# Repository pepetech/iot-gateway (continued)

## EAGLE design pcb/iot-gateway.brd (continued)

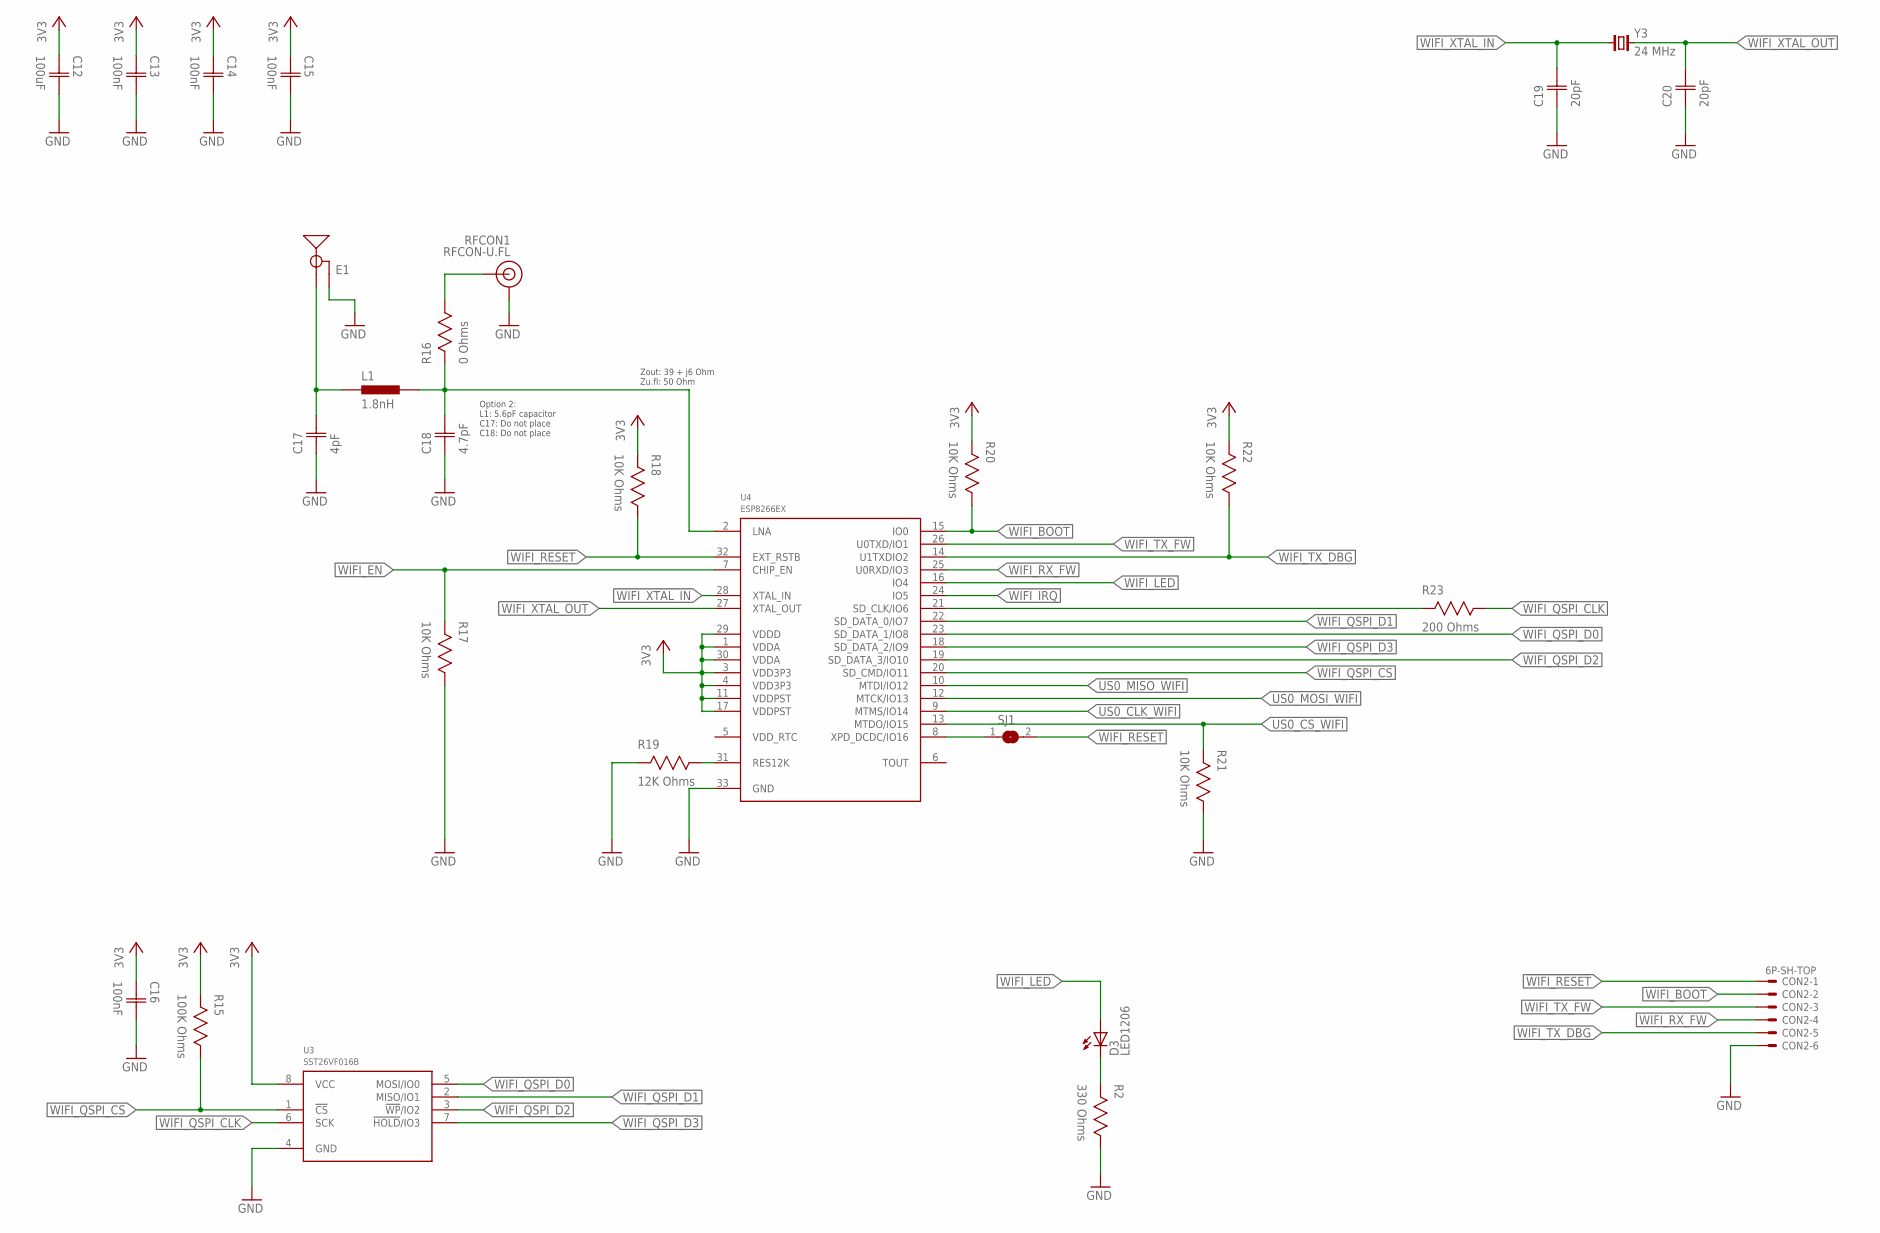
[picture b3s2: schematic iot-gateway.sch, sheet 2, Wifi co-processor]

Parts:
C12: 100uF; CAP1206
C13, C14, C15, C16: 100nF; CAP0603
C17: 4pF; CAP0603
C18: 4.7pF; CAP0603
C19, C20: 20pF; CAP0603
CON2: 6P-SH-TOP; SH-06-TOP
D3: LED1206; 1206
E1: 2.4GHZTRACE-15.2MM; TRACE_ANTENNA_2.4GHZ_15.2MM
L1: 1.8nH; IND0603
R2: 330 Ohms; RES0603
R15: 100K Ohms; RES0603
R16: 0 Ohms; RES0603
R17, R18, R20, R21, R22: 10K Ohms; RES0603
R19: 12K Ohms; RES0603
R23: 200 Ohms; RES0603
RFCON1: RFCON-U.FL; U.FL
SJ1: SJS; SJ_S
U3: SST26VF016B; WSOIC8
U4: ESP8266EX; QFN32
Y3: 24 MHz; 2-SMD-5032

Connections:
3V3: C12.1 (C1), C13.1 (C1), C14.1 (C1), C15.1 (C1), C16.1 (C1), R15.2, R18.2, R20.2, R22.2, U3.8 (VCC), U4.1 (VDDA), U4.3 (VDD3P3), U4.4 (VDD3P3), U4.11 (VDDPST), U4.17 (VDDPST), U4.29 (VDDD), U4.30 (VDDA); also elsewhere on the board
!WIFI_RESET: CON2.1, R18.1, SJ1.2, U4.32 (EXT_RSTB)
GND: C12.2 (C2), C13.2 (C2), C14.2 (C2), C15.2 (C2), C16.2 (C2), C17.1 (C1), C18.1 (C1), C19.1 (C1), C20.1 (C1), CON2.6, E1.GND, R2.1, R17.1, R19.2, R21.1, RFCON1.P$1 (GND), RFCON1.P$2 (GND), U3.4 (GND), U4.33 (GND); also elsewhere on the board
unnamed: R19.1, U4.31 (RES12K)
unnamed: R23.2, U4.21 (SD_CLK/IO6)
unnamed: C18.2 (C2), L1.2, R16.2, U4.2 (LNA)
unnamed: C17.2 (C2), E1.ANT (SIGNAL), L1.1
unnamed: R16.1, RFCON1.P$3 (SIGNAL)
unnamed: SJ1.1, U4.8 (XPD_DCDC/IO16)
unnamed: D3.1 (C), R2.2
US0_CLK_WIFI: U4.9 (MTMS/IO14)
US0_CS_WIFI: R21.2, U4.13 (MTDO/IO15)
US0_MISO_WIFI: U4.10 (MTDI/IO12)
US0_MOSI_WIFI: U4.12 (MTCK/IO13)
WIFI_BOOT: CON2.2, R20.1, U4.15 (IO0)
WIFI_EN: R17.2, U4.7 (CHIP_EN)
WIFI_IRQ: U4.24 (IO5)
WIFI_LED: D3.2 (A), U4.16 (IO4)
WIFI_QSPI_CLK: R23.1, U3.6 (SCK)
WIFI_QSPI_CS: R15.1, U3.1 (!CS!), U4.20 (SD_CMD/IO11)
WIFI_QSPI_D0: U3.5 (MOSI/IO0), U4.23 (SD_DATA_1/IO8)
WIFI_QSPI_D1: U3.2 (MISO/IO1), U4.22 (SD_DATA_0/IO7)
WIFI_QSPI_D2: U3.3 (!WP!/IO2), U4.19 (SD_DATA_3/IO10)
WIFI_QSPI_D3: U3.7 (!HOLD!/IO3), U4.18 (SD_DATA_2/IO9)
WIFI_RX_FW: CON2.4, U4.25 (U0RXD/IO3)
WIFI_TX_DBG: CON2.5, R22.1, U4.14 (U1TXDIO2)
WIFI_TX_FW: CON2.3, U4.26 (U0TXD/IO1)
WIFI_XTAL_IN: C19.2 (C2), U4.28 (XTAL_IN), Y3.1
WIFI_XTAL_OUT: C20.2 (C2), U4.27 (XTAL_OUT), Y3.2

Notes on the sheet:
Option 2: L1: 5.6pF capacitor C17: Do not place C18: Do not place
Zout: 39 + j6 Ohm Zu.fl: 50 Ohm

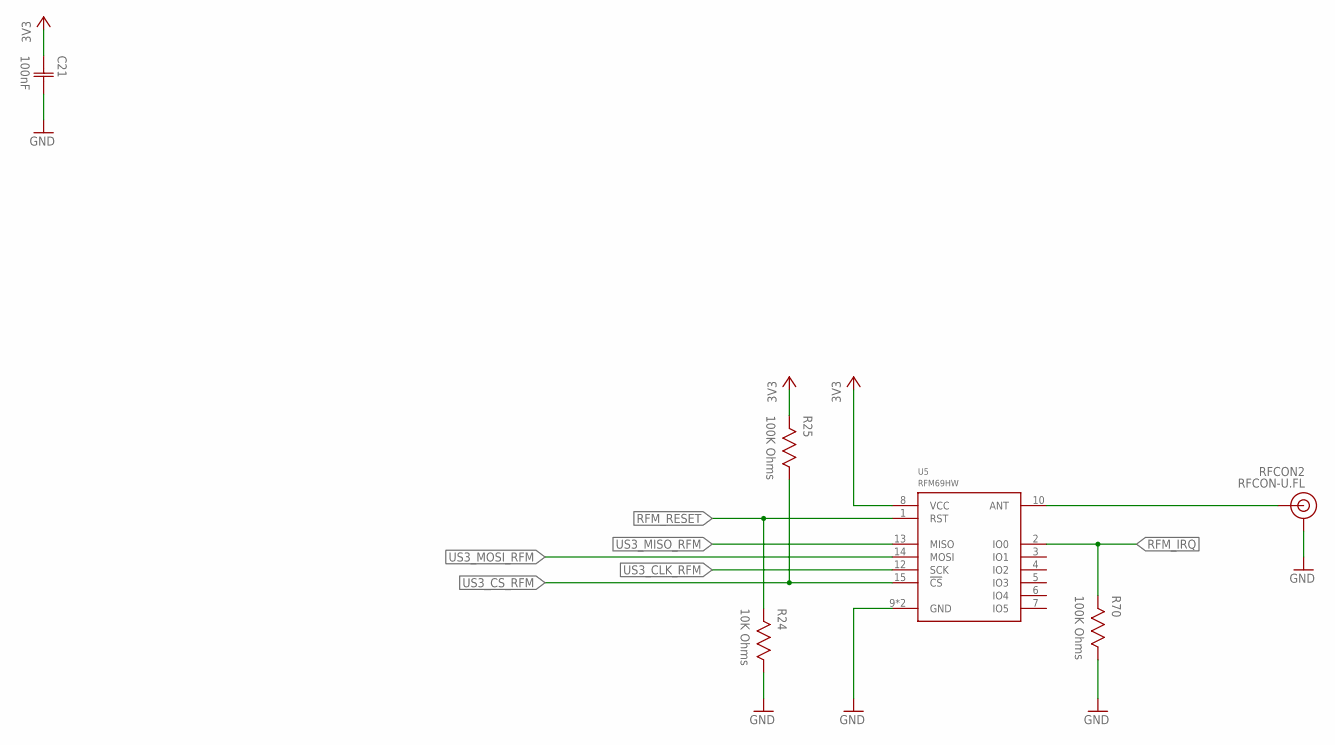
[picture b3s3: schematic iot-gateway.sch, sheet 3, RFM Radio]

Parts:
C21: 100nF; CAP0603
R24: 10K Ohms; RES0603
R25, R70: 100K Ohms; RES0603
RFCON2: RFCON-U.FL; U.FL
U5: RFM69HW; RFM69XW-XXXS2

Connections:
3V3: C21.1 (C1), R25.2, U5.8 (VCC); also elsewhere on the board
GND: C21.2 (C2), R24.1, R70.1, RFCON2.P$1 (GND), RFCON2.P$2 (GND), U5.9 (GND), U5.11 (GND); also elsewhere on the board
unnamed: RFCON2.P$3 (SIGNAL), U5.10 (ANT)
RFM_IRQ: R70.2, U5.2 (IO0)
RFM_RESET: R24.2, U5.1 (RST)
US3_CLK_RFM: U5.12 (SCK)
US3_CS_RFM: R25.1, U5.15 (!CS)
US3_MISO_RFM: U5.13 (MISO)
US3_MOSI_RFM: U5.14 (MOSI)

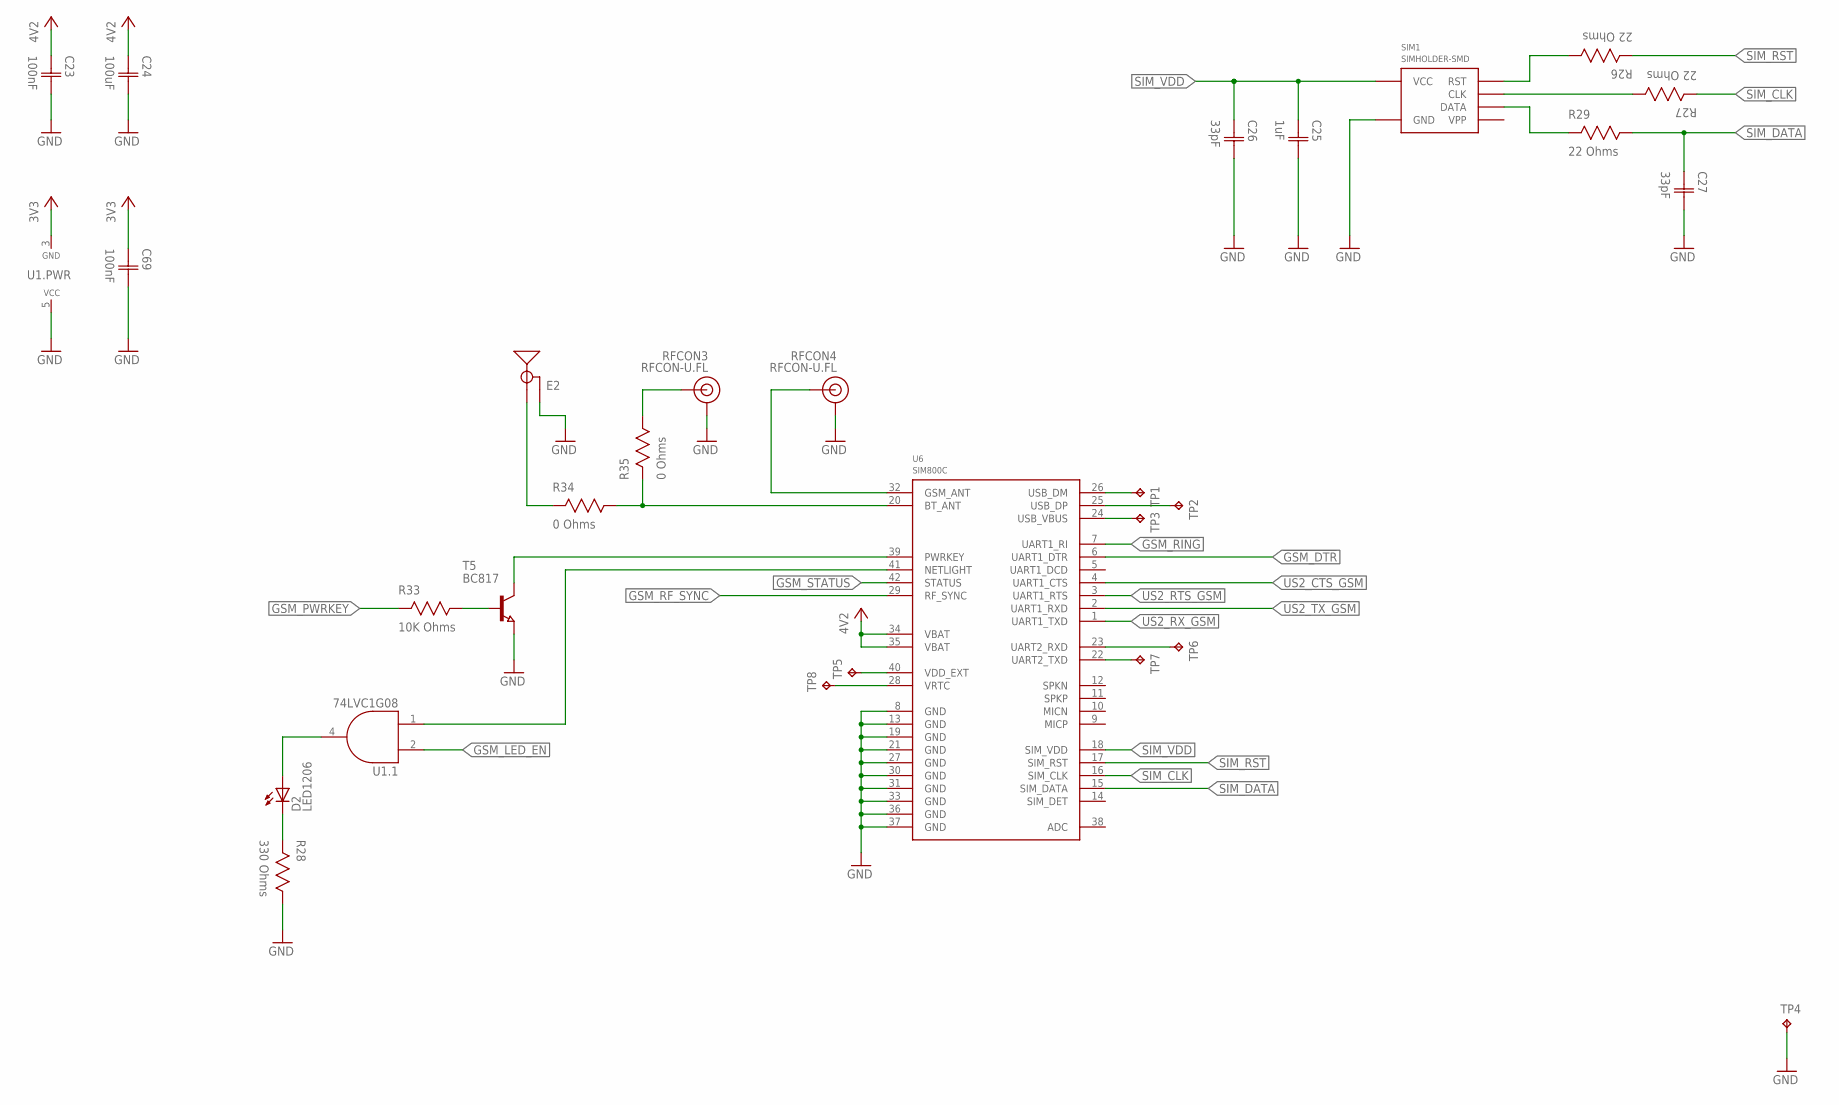
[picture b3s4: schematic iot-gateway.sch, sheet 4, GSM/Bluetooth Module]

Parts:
C23, C69: 100nF; CAP0603
C24: 100uF; CAP1206
C25: 1uF; CAP0603
C26, C27: 33pF; CAP0603
D2: LED1206; 1206
E2: 2.4GHZTRACE-15.2MM; TRACE_ANTENNA_2.4GHZ_15.2MM
R26, R27, R29: 22 Ohms; RES0603
R28: 330 Ohms; RES0603
R33: 10K Ohms; RES0603
R34, R35: 0 Ohms; RES0603
RFCON3, RFCON4: RFCON-U.FL; U.FL
SIM1: SIMHOLDER-SMD
T5: BC817; SOT23
TP1, TP2, TP3, TP4, TP5, TP6, TP7, TP8: TESTPOINT-1.27MM; PAD1.27MM
U1: 74LVC1G08; SC70-5
U6: SIM800C

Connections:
3V3: C69.1 (C1), U1.3 (GND); also elsewhere on the board
4V2: C23.1 (C1), C24.1 (C1), U6.34 (VBAT), U6.35 (VBAT); also elsewhere on the board
!GSM_DTR: U6.6 (UART1_DTR)
!GSM_RING: U6.7 (UART1_RI)
GND: C23.2 (C2), C24.2 (C2), C25.2 (C2), C26.2 (C2), C27.2 (C2), C69.2 (C2), E2.GND, R28.1, RFCON3.P$1 (GND), RFCON3.P$2 (GND), RFCON4.P$1 (GND), RFCON4.P$2 (GND), SIM1.C5 (GND), T5.2 (E), TP4.TP, U1.5 (VCC), U6.8 (GND), U6.13 (GND), U6.19 (GND), U6.21 (GND), U6.27 (GND), U6.30 (GND), U6.31 (GND), U6.33 (GND), U6.36 (GND), U6.37 (GND); also elsewhere on the board
GSM_LED_EN: U1.2 (A)
GSM_PWRKEY: R33.2
GSM_RF_SYNC: U6.29 (RF_SYNC)
GSM_STATUS: U6.42 (STATUS)
unnamed: RFCON4.P$3 (SIGNAL), U6.32 (GSM_ANT)
unnamed: R26.1, SIM1.C2 (RST)
unnamed: U1.1 (B), U6.41 (NETLIGHT)
unnamed: D2.1 (C), R28.2
unnamed: D2.2 (A), U1.4 (Y)
unnamed: R27.1, SIM1.C3 (CLK)
unnamed: R34.1, R35.2, U6.20 (BT_ANT)
unnamed: E2.ANT (SIGNAL), R34.2
unnamed: R35.1, RFCON3.P$3 (SIGNAL)
unnamed: TP8.TP, U6.28 (VRTC)
unnamed: TP1.TP, U6.26 (USB_DM)
unnamed: TP2.TP, U6.25 (USB_DP)
unnamed: T5.3 (C), U6.39 (PWRKEY)
unnamed: R33.1, T5.1 (B)
unnamed: TP3.TP, U6.24 (USB_VBUS)
unnamed: TP5.TP, U6.40 (VDD_EXT)
unnamed: R29.2, SIM1.C7 (DATA)
unnamed: TP6.TP, U6.23 (UART2_RXD)
unnamed: TP7.TP, U6.22 (UART2_TXD)
SIM_CLK: R27.2, U6.16 (SIM_CLK)
SIM_DATA: C27.1 (C1), R29.1, U6.15 (SIM_DATA)
SIM_RST: R26.2, U6.17 (SIM_RST)
SIM_VDD: C25.1 (C1), C26.1 (C1), SIM1.C1 (VCC), U6.18 (SIM_VDD)
US2_CTS_GSM: U6.4 (UART1_CTS)
US2_RTS_GSM: U6.3 (UART1_RTS)
US2_RX_GSM: U6.1 (UART1_TXD)
US2_TX_GSM: U6.2 (UART1_RXD)

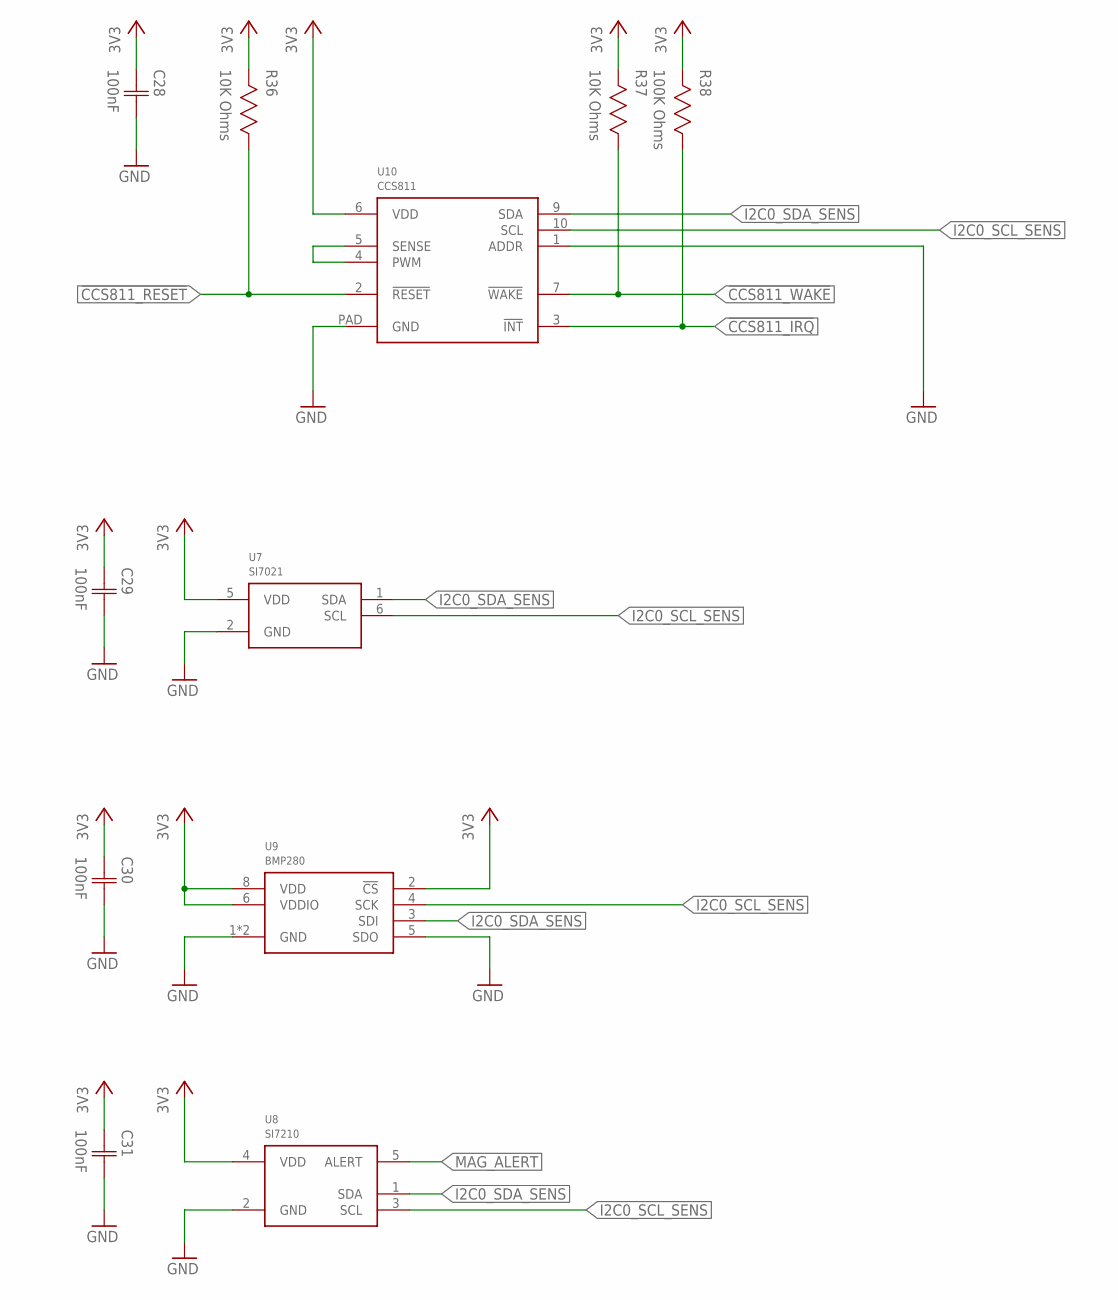
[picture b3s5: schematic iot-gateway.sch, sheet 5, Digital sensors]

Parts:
C28, C29, C30, C31: 100nF; CAP0603
R36, R37: 10K Ohms; RES0603
R38: 100K Ohms; RES0603
U7: SI7021; DFN6
U8: SI7210; SOT23-5
U9: BMP280
U10: CCS811; LGA10

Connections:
3V3: C28.1 (C1), C29.1 (C1), C30.1 (C1), C31.1 (C1), R36.2, R37.2, R38.2, U7.5 (VDD), U8.4 (VDD), U9.2 (!CS), U9.6 (VDDIO), U9.8 (VDD), U10.6 (VDD); also elsewhere on the board
!CCS811_IRQ: R38.1, U10.3 (!INT)
!CCS811_RESET: R36.1, U10.2 (!RESET)
!CCS811_WAKE: R37.1, U10.7 (!WAKE)
GND: C28.2 (C2), C29.2 (C2), C30.2 (C2), C31.2 (C2), U7.2 (GND), U8.2 (GND), U9.1 (GND), U9.5 (SDO), U9.7 (GND), U10.1 (ADDR), U10.PAD (GND); also elsewhere on the board
I2C0_SCL_SENS: U7.6 (SCL), U8.3 (SCL), U9.4 (SCK), U10.10 (SCL); also elsewhere on the board
I2C0_SDA_SENS: U7.1 (SDA), U8.1 (SDA), U9.3 (SDI), U10.9 (SDA); also elsewhere on the board
MAG_ALERT: U8.5 (ALERT)
unnamed: U10.4 (PWM), U10.5 (SENSE)

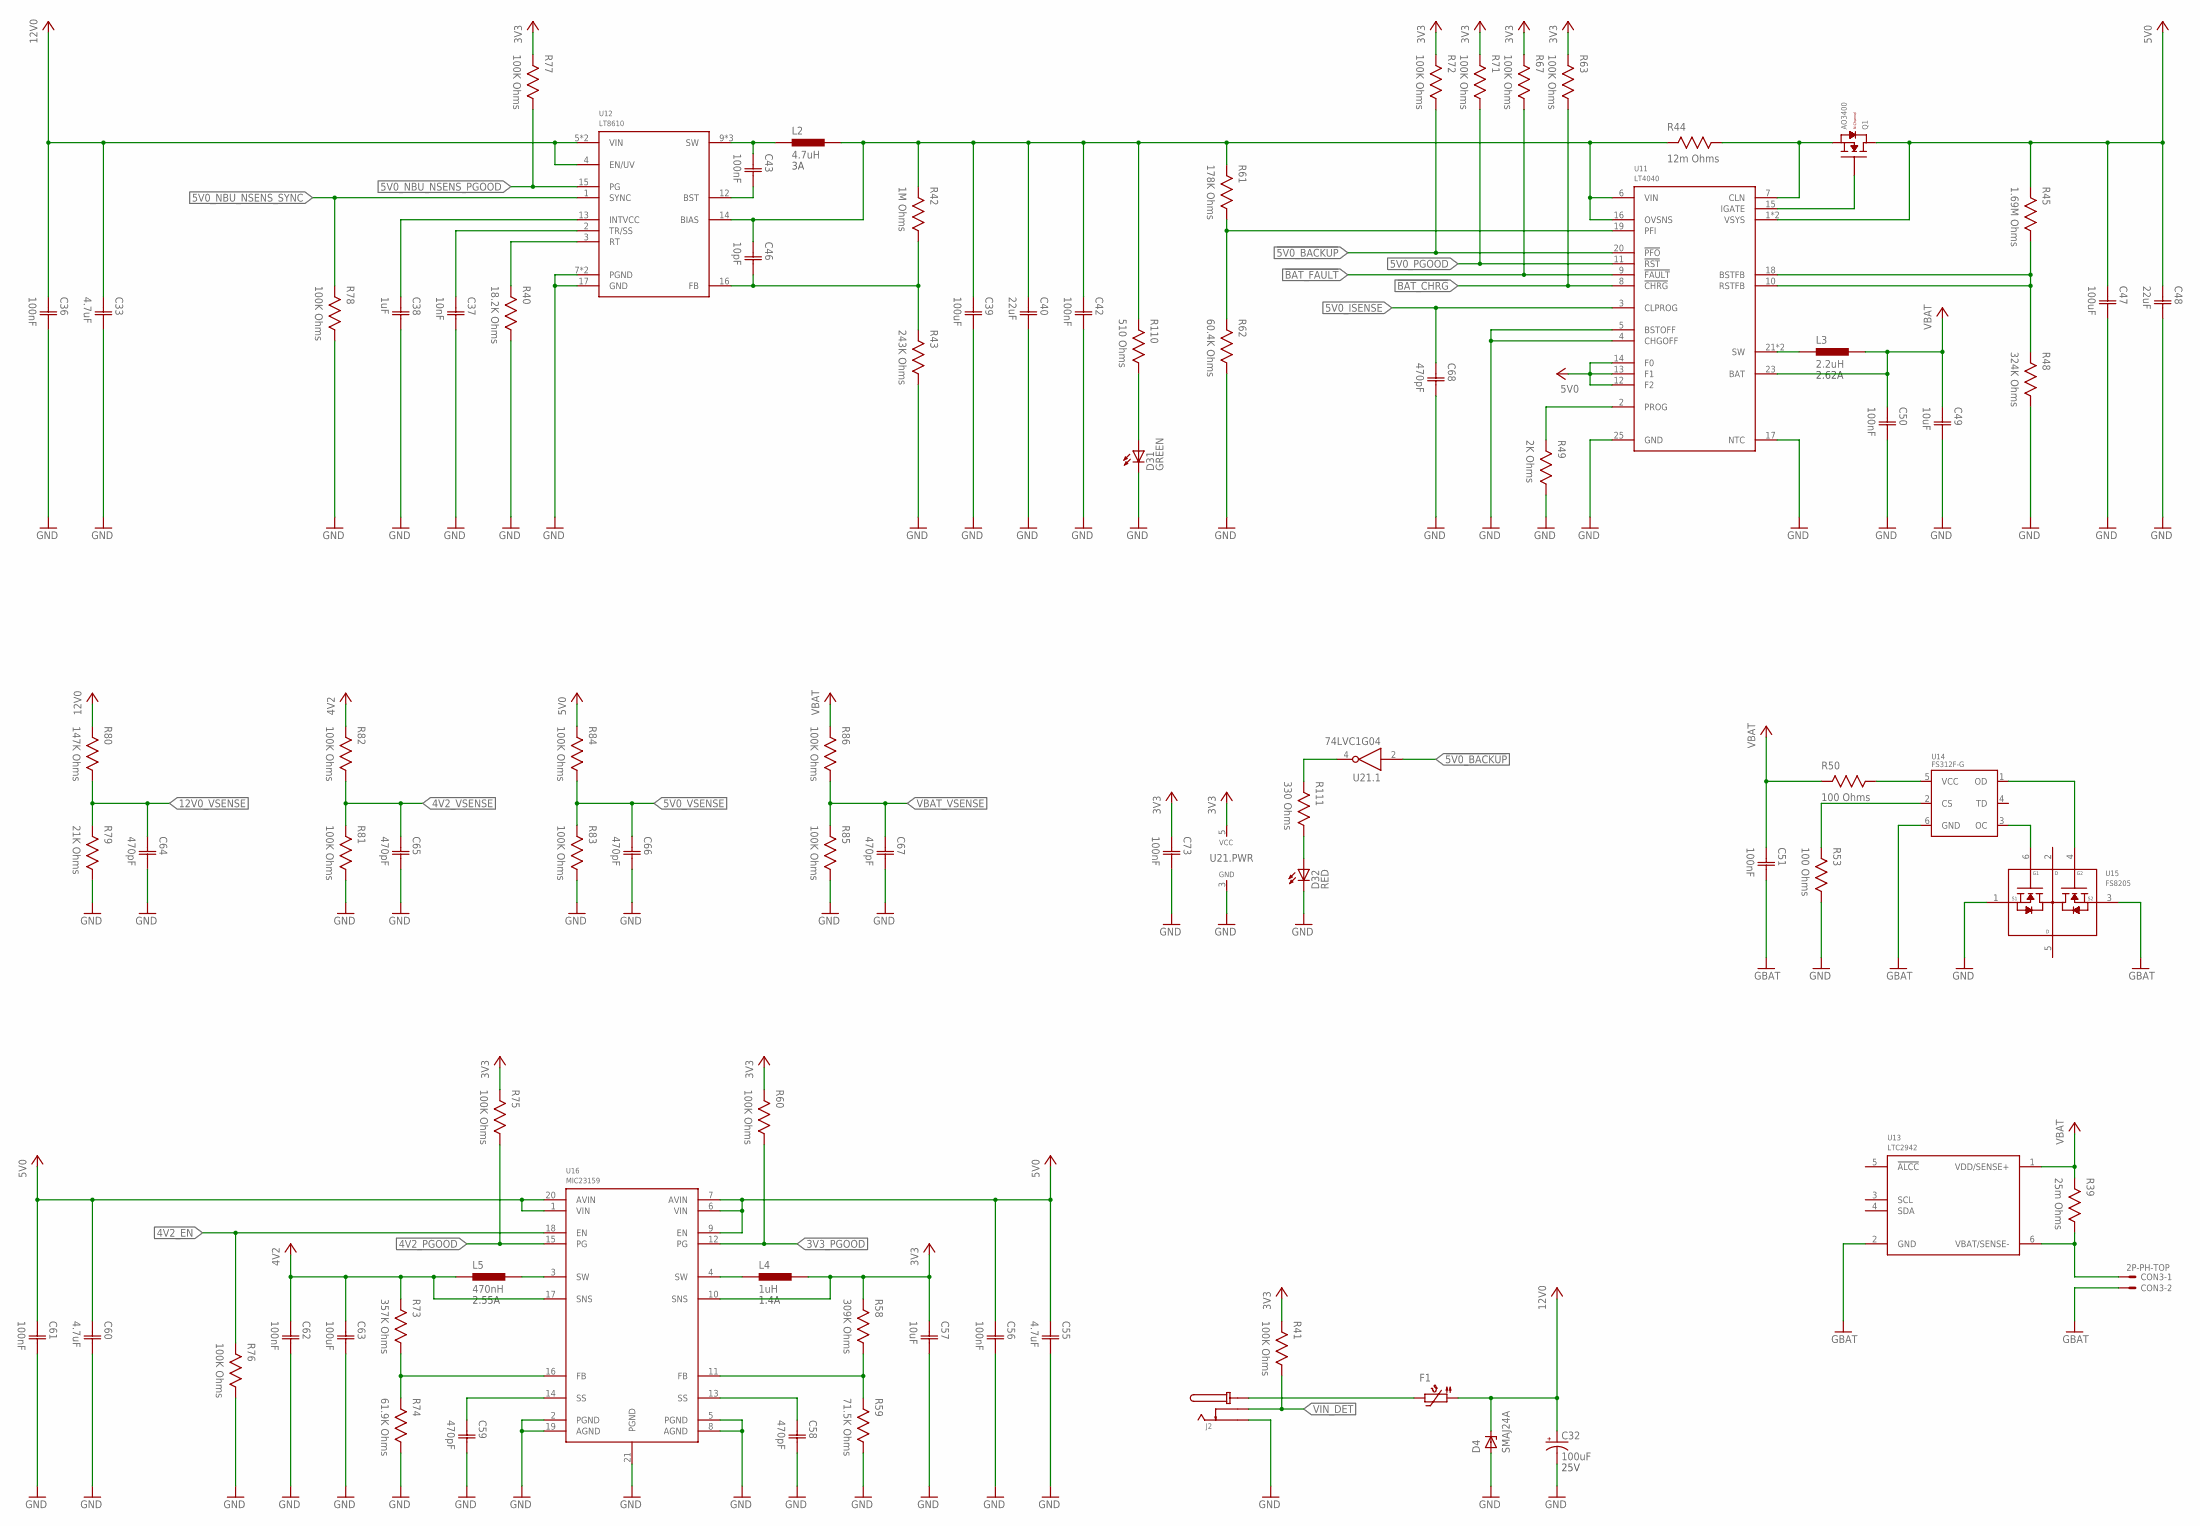
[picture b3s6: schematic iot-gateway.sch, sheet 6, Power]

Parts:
C32: 100uF; AL-CAP-CASE-D; VOLTAGE 25V
C33, C55, C60: 4.7uF; CAP0603
C36, C42, C43, C50, C51, C56, C61, C62, C73: 100nF; CAP0603
C37: 10nF; CAP0603
C38: 1uF; CAP0603
C39, C47, C63: 100uF; CAP1206
C40, C48: 22uF; CAP1206
C46: 10pF; CAP0603
C49, C57: 10uF; CAP0603
C58, C59, C64, C65, C66, C67, C68: 470pF; CAP0603
CON3: 2P-PH-TOP; PH-02-TOP
D4: SMAJ24A; DO214AC
D31: GREEN; 0603
D32: RED; 0603
F1: 2.6A Hold; 1812
J2: DCJACK; DC-050
L2: 4.7uH; IND0606
L3: 2.2uH; IND0505
L4: 1uH; IND0805
L5: 470nH; IND3225
Q1: AO3400; SOT23
R39: 25m Ohms; RES1206
R40: 18.2K Ohms; RES0603
R41, R60, R63, R67, R71, R72, R75, R76, R77, R78, R81, R82, R83, R84, R85, R86: 100K Ohms; RES0603
R42: 1M Ohms; RES0603
R43: 243K Ohms; RES0603
R44: 12m Ohms; RES1206
R45: 1.69M Ohms; RES0603
R48: 324K Ohms; RES0603
R49: 2K Ohms; RES0603
R50, R53: 100 Ohms; RES0603
R58: 309K Ohms; RES0603
R59: 71.5K Ohms; RES0603
R61: 178K Ohms; RES0603
R62: 60.4K Ohms; RES0603
R73: 357K Ohms; RES0603
R74: 61.9K Ohms; RES0603
R79: 21K Ohms; RES0603
R80: 147K Ohms; RES0603
R110: 510 Ohms; RES0603
R111: 330 Ohms; RES0603
U11: LT4040; QFN24_ASYM
U12: LT8610; MSOP16_EP
U13: LTC2942; DFN6
U14: FS312F-G; SOT23-6
U15: FS8205; SOT23-6
U16: MIC23159; VQFN20
U21: 74LVC1G04; SC70-5

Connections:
3V3: C57.1 (C1), C73.1 (C1), L4.2, R41.2, R58.2, R60.2, R63.2, R67.2, R71.2, R72.2, R75.2, R77.2, U16.10 (SNS), U21.5 (VCC); also elsewhere on the board
3V3_FB: R58.1, R59.2, U16.11 (FB)
3V3_PGOOD: R60.1, U16.12 (PG)
4V2: C62.1 (C1), C63.1 (C1), L5.1, R73.2, R82.2, U16.17 (SNS); also elsewhere on the board
4V2_EN: R76.2, U16.18 (EN)
4V2_FB: R73.1, R74.2, U16.16 (FB)
4V2_PGOOD: R75.1, U16.15 (PG)
4V2_VSENSE: C65.1 (C1), R81.2, R82.1
5V0: C47.1 (C1), C48.1 (C1), C55.1 (C1), C56.1 (C1), C60.1 (C1), C61.1 (C1), Q1.3 (D), R45.2, R84.2, U11.1 (VSYS), U11.12 (F2), U11.13 (F1), U11.14 (F0), U11.24 (VSYS), U16.1 (VIN), U16.6 (VIN), U16.7 (AVIN), U16.9 (EN), U16.20 (AVIN); also elsewhere on the board
5V0_FB: R45.1, R48.2, U11.10 (RSTFB), U11.18 (BSTFB)
5V0_ISENSE: C68.1 (C1), U11.3 (CLPROG)
5V0_NBU: Q1.2 (S), R44.1, U11.7 (CLN)
5V0_NBU_NSENS: C39.1 (C1), C40.1 (C1), C42.1 (C1), C46.1 (C1), L2.2, R42.2, R44.2, R61.2, R110.2, U11.6 (VIN), U11.16 (OVSNS), U12.14 (BIAS)
5V0_NBU_NSENS_FB: C46.2 (C2), R42.1, R43.2, U12.16 (FB)
5V0_NBU_NSENS_PGOOD: R77.1, U12.15 (PG)
5V0_NBU_NSENS_SYNC: R78.2, U12.1 (SYNC)
5V0_PGOOD: R71.1, U11.11 (!RST)
5V0_VSENSE: C66.1 (C1), R83.2, R84.1
12V0: C32.1 (+), C33.1 (C1), C36.1 (C1), D4.C, F1.1, R80.2, U12.4 (EN/UV), U12.5 (VIN), U12.6 (VIN)
12V0_UNFUSED: F1.2, J2.C, J2.C' (C)
12V0_VSENSE: C64.1 (C1), R79.2, R80.1
!5V0_BACKUP: R72.1, U11.20 (!PFO), U21.2 (A)
!BAT_CHRG: R63.1, U11.8 (!CHRG)
!BAT_FAULT: R67.1, U11.9 (!FAULT)
GBAT: C51.2 (C2), CON3.2, U13.2 (GND), U14.6 (GND), U15.3 (S2)
GND: C32.2 (-), C33.2 (C2), C36.2 (C2), C37.2 (C2), C38.2 (C2), C39.2 (C2), C40.2 (C2), C42.2 (C2), C47.2 (C2), C48.2 (C2), C49.2 (C2), C50.2 (C2), C55.2 (C2), C56.2 (C2), C57.2 (C2), C58.2 (C2), C59.2 (C2), C60.2 (C2), C61.2 (C2), C62.2 (C2), C63.2 (C2), C64.2 (C2), C65.2 (C2), C66.2 (C2), C67.2 (C2), C68.2 (C2), C73.2 (C2), D4.A, D31.1 (C), D32.1 (C), J2.O, R40.1, R43.1, R48.1, R49.1, R53.1, R59.1, R62.1, R74.1, R76.1, R78.1, R79.1, R81.1, R83.1, R85.1, U11.4 (CHGOFF), U11.5 (BSTOFF), U11.17 (NTC), U11.25 (GND), U12.7 (PGND), U12.8 (PGND), U12.17 (GND), U15.1 (S1), U16.2 (PGND), U16.5 (PGND), U16.8 (AGND), U16.19 (AGND), U16.21 (PGND), U21.3 (GND); also elsewhere on the board
unnamed: R40.2, U12.3 (RT)
unnamed: C37.1 (C1), U12.2 (TR/SS)
unnamed: C38.1 (C1), U12.13 (INTVCC)
unnamed: C43.1 (C1), L2.1, U12.9 (SW), U12.10 (SW), U12.11 (SW)
unnamed: C43.2 (C2), U12.12 (BST)
unnamed: Q1.1 (G), U11.15 (IGATE)
unnamed: L3.1, U11.21 (SW), U11.22 (SW)
unnamed: R49.2, U11.2 (PROG)
unnamed: R50.1, U14.5 (VCC)
unnamed: R53.2, U14.2 (CS)
unnamed: U14.3 (OC), U15.6 (G1)
unnamed: U14.1 (OD), U15.4 (G2)
unnamed: L4.1, U16.4 (SW)
unnamed: C58.1 (C1), U16.13 (SS)
unnamed: C59.1 (C1), U16.14 (SS)
unnamed: L5.2, U16.3 (SW)
unnamed: R111.2, U21.4 (Y)
unnamed: D31.2 (A), R110.1
unnamed: D32.2 (A), R111.1
PF_THRESH: R61.1, R62.2, U11.19 (PFI)
VBAT: C49.1 (C1), C50.1 (C1), C51.1 (C1), L3.2, R39.2, R50.2, R86.2, U11.23 (BAT), U13.1 (VDD/SENSE+)
VBAT_NSENS: CON3.1, R39.1, U13.6 (VBAT/SENSE-)
VBAT_VSENSE: C67.1 (C1), R85.2, R86.1
VIN_DET: J2.DT, R41.1

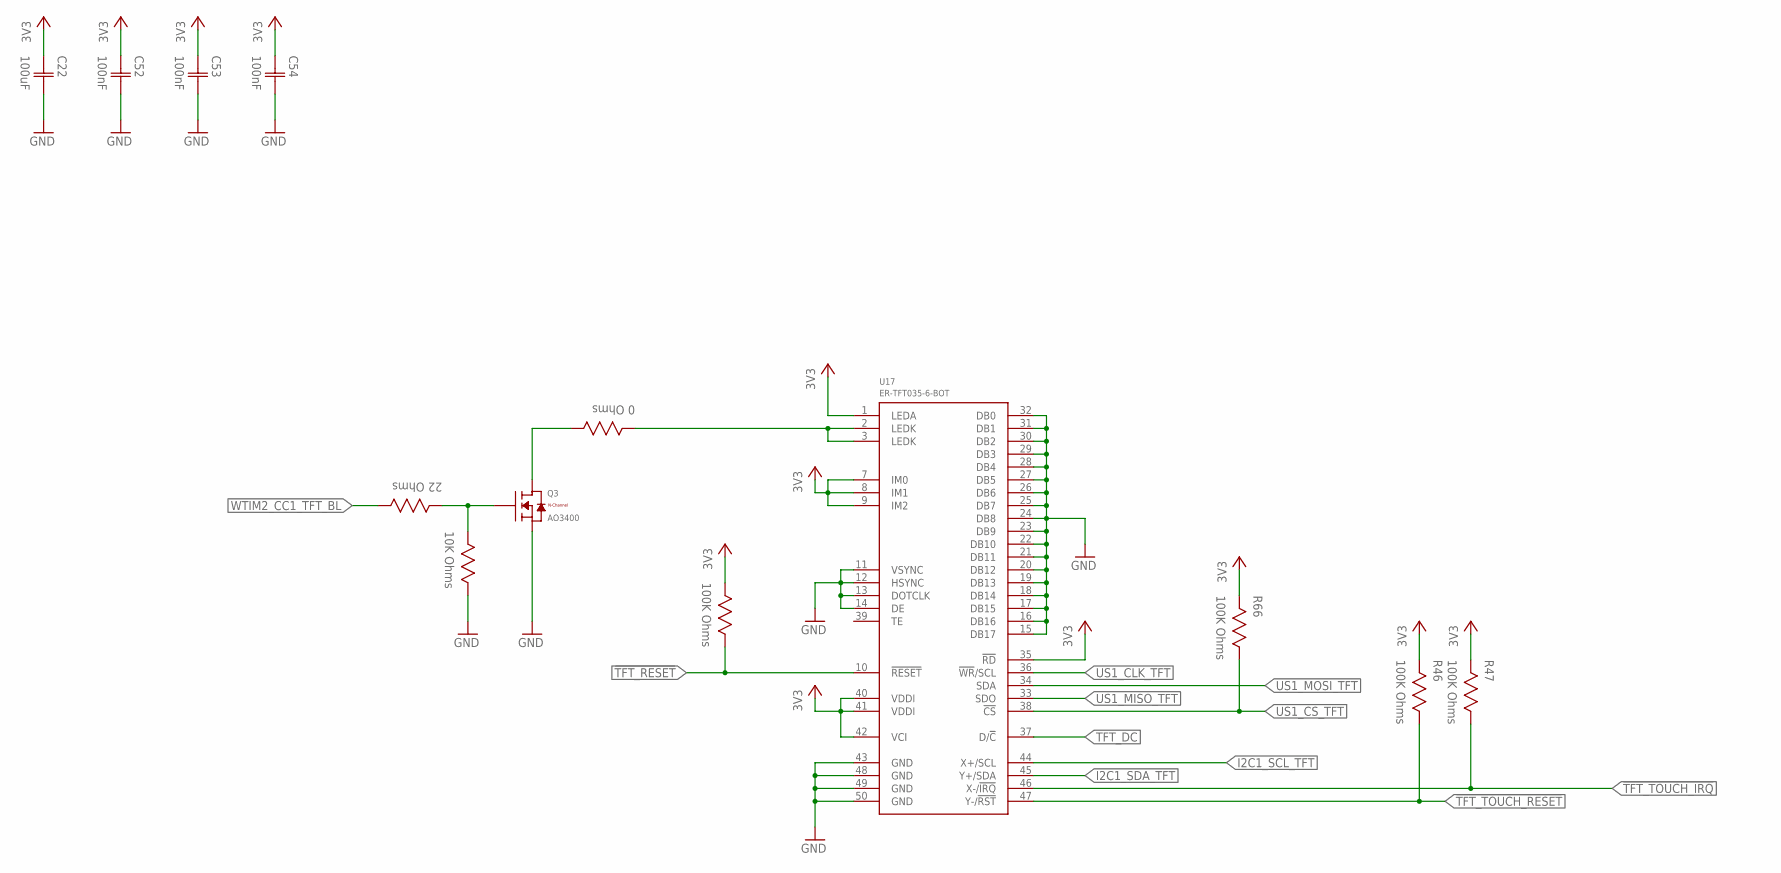
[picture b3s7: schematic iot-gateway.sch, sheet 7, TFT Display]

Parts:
C22: 100uF; CAP1206
C52, C53, C54: 100nF; CAP0603
Q3: AO3400; SOT23
R30: 22 Ohms; RES0603
R31: 10K Ohms; RES0603
R32, R46, R47, R66: 100K Ohms; RES0603
R64: 0 Ohms; RES0603
U17: ER-TFT035-6-BOT; FPC-50P-TFT-BOT

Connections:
3V3: C22.1 (C1), C52.1 (C1), C53.1 (C1), C54.1 (C1), R32.2, R46.2, R47.2, R66.2, U17.1 (LEDA), U17.7 (IM0), U17.8 (IM1), U17.9 (IM2), U17.35 (!RD), U17.40 (VDDI), U17.41 (VDDI), U17.42 (VCI); also elsewhere on the board
!TFT_RESET: R32.1, U17.10 (!RESET)
!TFT_TOUCH_IRQ: R47.1, U17.46 (X-/!IRQ!)
!TFT_TOUCH_RESET: R46.1, U17.47 (Y-/!RST!)
GND: C22.2 (C2), C52.2 (C2), C53.2 (C2), C54.2 (C2), Q3.2 (S), R31.1, U17.11 (VSYNC), U17.12 (HSYNC), U17.13 (DOTCLK), U17.14 (DE), U17.15 (DB17), U17.16 (DB16), U17.17 (DB15), U17.18 (DB14), U17.19 (DB13), U17.20 (DB12), U17.21 (DB11), U17.22 (DB10), U17.23 (DB9), U17.24 (DB8), U17.25 (DB7), U17.26 (DB6), U17.27 (DB5), U17.28 (DB4), U17.29 (DB3), U17.30 (DB2), U17.31 (DB1), U17.32 (DB0), U17.43 (GND), U17.48 (GND), U17.49 (GND), U17.50 (GND); also elsewhere on the board
I2C1_SCL_TFT: U17.44 (X+/SCL); also elsewhere on the board
I2C1_SDA_TFT: U17.45 (Y+/SDA); also elsewhere on the board
unnamed: Q3.1 (G), R30.2, R31.2
unnamed: Q3.3 (D), R64.1
unnamed: R64.2, U17.2 (LEDK), U17.3 (LEDK)
TFT_DC: U17.37 (D/!C!)
US1_CLK_TFT: U17.36 (!WR!/SCL)
US1_CS_TFT: R66.1, U17.38 (!CS)
US1_MISO_TFT: U17.33 (SDO)
US1_MOSI_TFT: U17.34 (SDA)
WTIM2_CC1_TFT_BL: R30.1

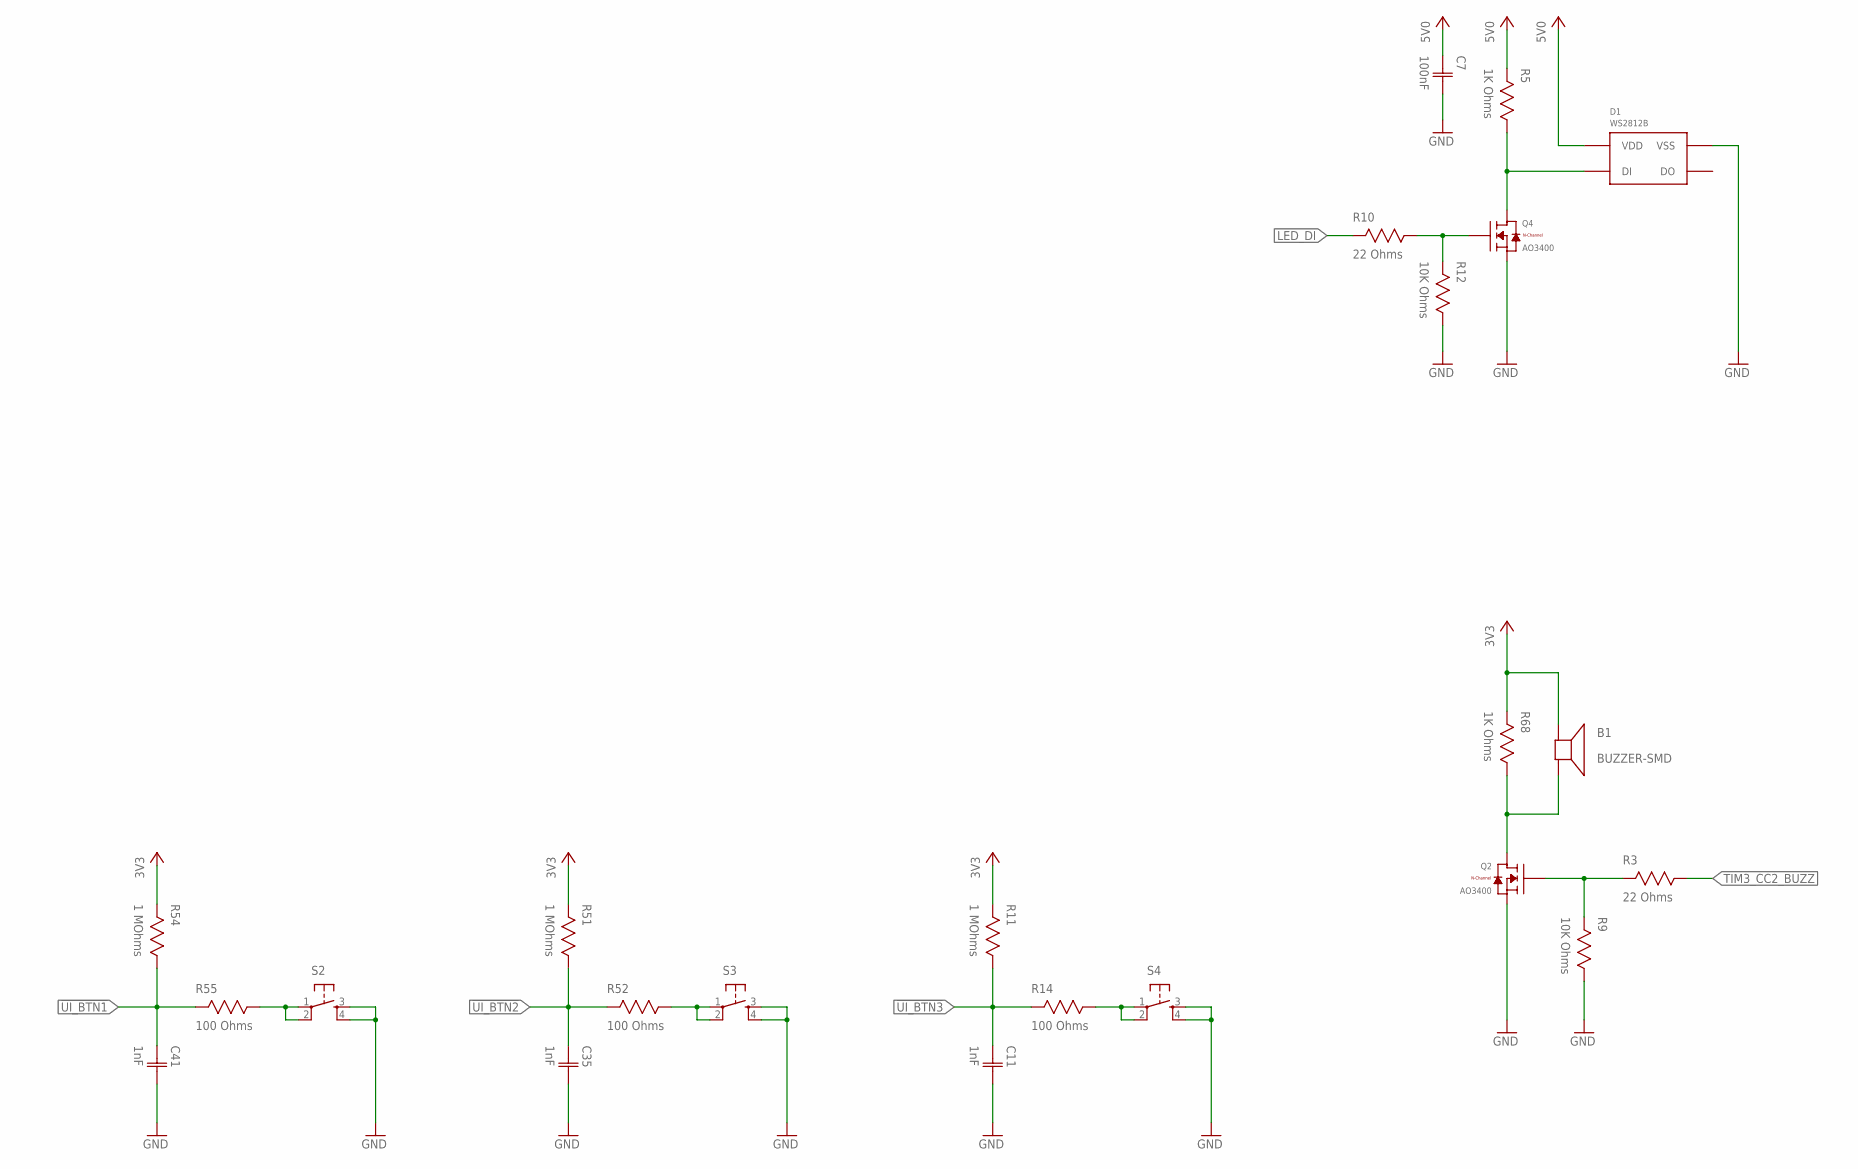
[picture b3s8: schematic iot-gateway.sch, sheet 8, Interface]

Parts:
B1: BUZZER-SMD; SMD
C7: 100nF; CAP0603
C11, C35, C41: 1nF; CAP0603
D1: WS2812B; WS2812B-SMD5050
Q2, Q4: AO3400; SOT23
R3, R10: 22 Ohms; RES0603
R5, R68: 1K Ohms; RES0603
R9, R12: 10K Ohms; RES0603
R11, R51, R54: 1 MOhms; RES0603
R14, R52, R55: 100 Ohms; RES0603
S2, S3, S4: TAC_SWITCHSMD_4.5X4.5; TAC_SW_SMD_4.5X4.5

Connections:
3V3: B1.1 (+), R11.2, R51.2, R54.2, R68.2; also elsewhere on the board
5V0: C7.1 (C1), D1.1 (VDD), R5.2; also elsewhere on the board
!UI_BTN1: C41.1 (C1), R54.1, R55.2
!UI_BTN2: C35.1 (C1), R51.1, R52.2
!UI_BTN3: C11.1 (C1), R11.1, R14.2
GND: C7.2 (C2), C11.2 (C2), C35.2 (C2), C41.2 (C2), D1.3 (VSS), Q2.2 (S), Q4.2 (S), R9.1, R12.1, S2.3, S2.4, S3.3, S3.4, S4.3, S4.4; also elsewhere on the board
LED_DI: R10.2
unnamed: D1.4 (DI), Q4.3 (D), R5.1
unnamed: Q2.1 (G), R3.2, R9.2
unnamed: B1.2 (-), Q2.3 (D), R68.1
unnamed: Q4.1 (G), R10.1, R12.2
unnamed: R52.1, S3.1, S3.2
unnamed: R14.1, S4.1, S4.2
unnamed: R55.1, S2.1, S2.2
TIM3_CC2_BUZZ: R3.1

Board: 2 copper layers, 216 parts (7 on the bottom side), 138 nets, no tracks yet.
